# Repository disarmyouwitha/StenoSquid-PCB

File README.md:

# Steno Squid PCB

**ZMK firmware for StenoSquid-PCB!: https://github.com/disarmyouwitha/StenoSquid**

Steno Squid adds 16 MB (or 64MB) of flash for onboard stenography to your **Boardsource Wireless Corne SMT**.\
Steno Squid sits on top of the switch plate and connects through the eight-contact expansion slot.

## Choose a board

Both DIY boards use exposed SOIC leads and 0805 passives. Order a bare PCB using the ZIP for your chosen capacity and artwork.

| Capacity | Flash package | Board files | Parts | Est. total build (USD) |
|---|---|---|---|---:|
| **16 MB** | [Winbond W25Q128JVSIQ, SOIC-8 (208 mil)](https://www.digikey.com/en/products/detail/winbond-electronics/W25Q128JVSIQ-TR/5803944) | [White silkscreen ZIP](manufacturing/2026-11-18/diy-bare/stenosquid-16mb-diy-bare.zip) · [KiCad and fit template](variants/16mb-diy-soic/README.md) | [16 MB BOM](variants/16mb-diy-soic/BOM.csv) | **~$25** |
| **64 MB** | [Winbond W25Q512JVFIQ, SOIC-16 (300 mil)](https://www.digikey.com/en/products/detail/winbond-electronics/W25Q512JVFIQ/10244707) | [White silkscreen ZIP](manufacturing/2026-11-18/diy-bare/stenosquid-64mb-diy-bare.zip) · [KiCad and fit template](variants/64mb-diy-soic/README.md) | [64 MB BOM](variants/64mb-diy-soic/BOM.csv) | **~$35** |

### Parts for one board

| Ref. | Qty. | Part |
|---|---:|---|
| U1 | 1 | The Winbond flash listed for your PCB above |
| C1 | 1 | 100 nF X7R ceramic capacitor, 0805. BOM part Yageo [`CC0805KRX7R9BB104`](https://www.digikey.com/en/products/detail/yageo/CC0805KRX7R9BB104/302874) |
| R1 | 1 | 10 kΩ, 1% resistor, 0805. BOM part Yageo [`RC0805FR-0710KL`](https://www.digikey.com/en/products/detail/yageo/RC0805FR-0710KL/727535) |

## Factory-assembled 16 MB and 64 MB boards

The owner confirmed that both manufactured WSON boards worked. These low-profile builds have assembly packages for the flash, decoupling capacitor and CS# pull-up. Everything you need to have JLPCB manufacture it for you! (This was [much more expensive](https://github.com/disarmyouwitha/StenoSquid-PCB/blob/main/manufacturing/2026-11-18/cart-preview.jpg) than the DIY build!)

| **16 MB · White silkscreen** | **64 MB · Gold ENIG artwork** |
|---|---|
|  |  |
| [KiCad and BOM](pcb/README.md) · [Gerber ZIP](manufacturing/2026-11-18/16mb-silkscreen/16mb-silkscreen-gerbers.zip) · [BOM and placement](manufacturing/2026-11-18/16mb-silkscreen/) | [KiCad and BOM](variants/64mb-enig/README.md) · [Gerber ZIP](manufacturing/2026-11-18/64mb-gold/64mb-gold-gerbers.zip) · [BOM and placement](manufacturing/2026-11-18/64mb-gold/) |

## Host wiring

Viewed from above, the contacts run along the bottom with pin 1 on the left.

| Contact | Host GPIO or rail | Signal |
|---|---|---|
| 1 | P0.07 | CS# |
| 2 | P0.21 | IO0 |
| 3 | P0.12 | IO3 |
| 4 | P0.23 | IO1 |
| 5 | VCC switched by P0.31 | VCC |
| 6 | GND | GND |
| 7 | P0.19 | CLK |
| 8 | P0.05 | IO2 |

## License

StenoSquid-PCB is open-source hardware licensed under the [CERN Open Hardware Licence Version 2 - Permissive (CERN-OHL-P-2.0)](LICENSE).

You are free to manufacture, modify, and sell these boards, subject to the license terms. Third-party artwork retain the respective rights and licenses.

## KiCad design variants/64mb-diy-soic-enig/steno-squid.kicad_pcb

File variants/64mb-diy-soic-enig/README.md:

# Steno Squid 64 MB DIY · gold ENIG

[KiCad project](steno-squid.kicad_pro) · [Bare-board ZIP](../../manufacturing/diy-enig/stenosquid-64mb-diy-enig-bare.zip) · [BOM](BOM.csv) · [Front](previews/front.png) · [Back](previews/back.png) · [Schematic](previews/steno-squid.svg) · [1:1 fit template](previews/plate-fit-1to1.svg) · [STEP](steno-squid.step) · [Validation](validation.json)

Order the bare-board ZIP with **black solder mask and ENIG surface finish**. Pop and the splats are exposed front copper with matching soldermask openings and a 1 mm front copper keepout. The [white silkscreen edition](../64mb-diy-soic/README.md) uses the same parts, connector and routing.

The 64 MB DIY production variant uses the **Winbond W25Q512JVFIQ** in a 300 mil SOIC-16 package. Its exposed gull-wing leads are on 1.27 mm pitch and there is no center pad. C1 is 100 nF and R1 is 10 kΩ, both 0805. C2 and R2 are omitted. Everything except the mating portion of the header mounts on the front. [Winbond pinout and package drawing, pp. 7 and 89](https://www.mouser.com/datasheet/2/949/Winbond_W25Q512JV_Datasheet-3240039.pdf).

The PCB is 21.78 × 44.82 mm and nominally 1.0 mm thick, with the same header centers as the 16 MB DIY board, with Pop in exposed gold. The chip can stand **2.64 mm above the PCB** and span **10.64 mm** across its leads. Use the actual-size template to check the outline, and the package dimensions or a real chip to check vertical clearance. The generic KiCad STEP model is for visualization.

| Host contact | Signal | SOIC-16 lead |
|---|---|---:|
| 1 | CS_N | 7 |
| 2 | IO0 | 15 |
| 3 | IO3 | 1 |
| 4 | IO1 | 8 |
| 5 | VCC_SW | 2 |
| 6 | GND | 10 |
| 7 | CLK | 16 |
| 8 | IO2 | 9 |

The dedicated RESET# lead (3) is tied to VCC_SW on the board. Leads 4–6 and 11–14 have isolated lands. Align U1's pin-1 indicator with the board's upper-left marker, tack one corner, check alignment, then solder the remaining leads. Inspect for bridges and verify continuity and no supply short before connecting to the host.

KiCad 10.0.7 reports zero ERC, DRC, unconnected items, and schematic parity issues with every category enabled. The [DIY validator](../../tools/check_diy_soic.py) also checks pad geometry, the header and flash pin maps, and the unchanged board outline. Final populated fit and powered bring-up are pending.

For first power-up, qualify the switched rail for this chip's 2.7–3.6 V range and its read/program/erase load. Check JEDEC ID `EF 40 20` and use firmware with 64 MiB support and four-byte addressing. Verify reads and writes across the `0x01000000` and `0x02000000` address boundaries and near the end of flash, including after power cycling. [Capacity and power review](../../docs/capacity-variants.md).

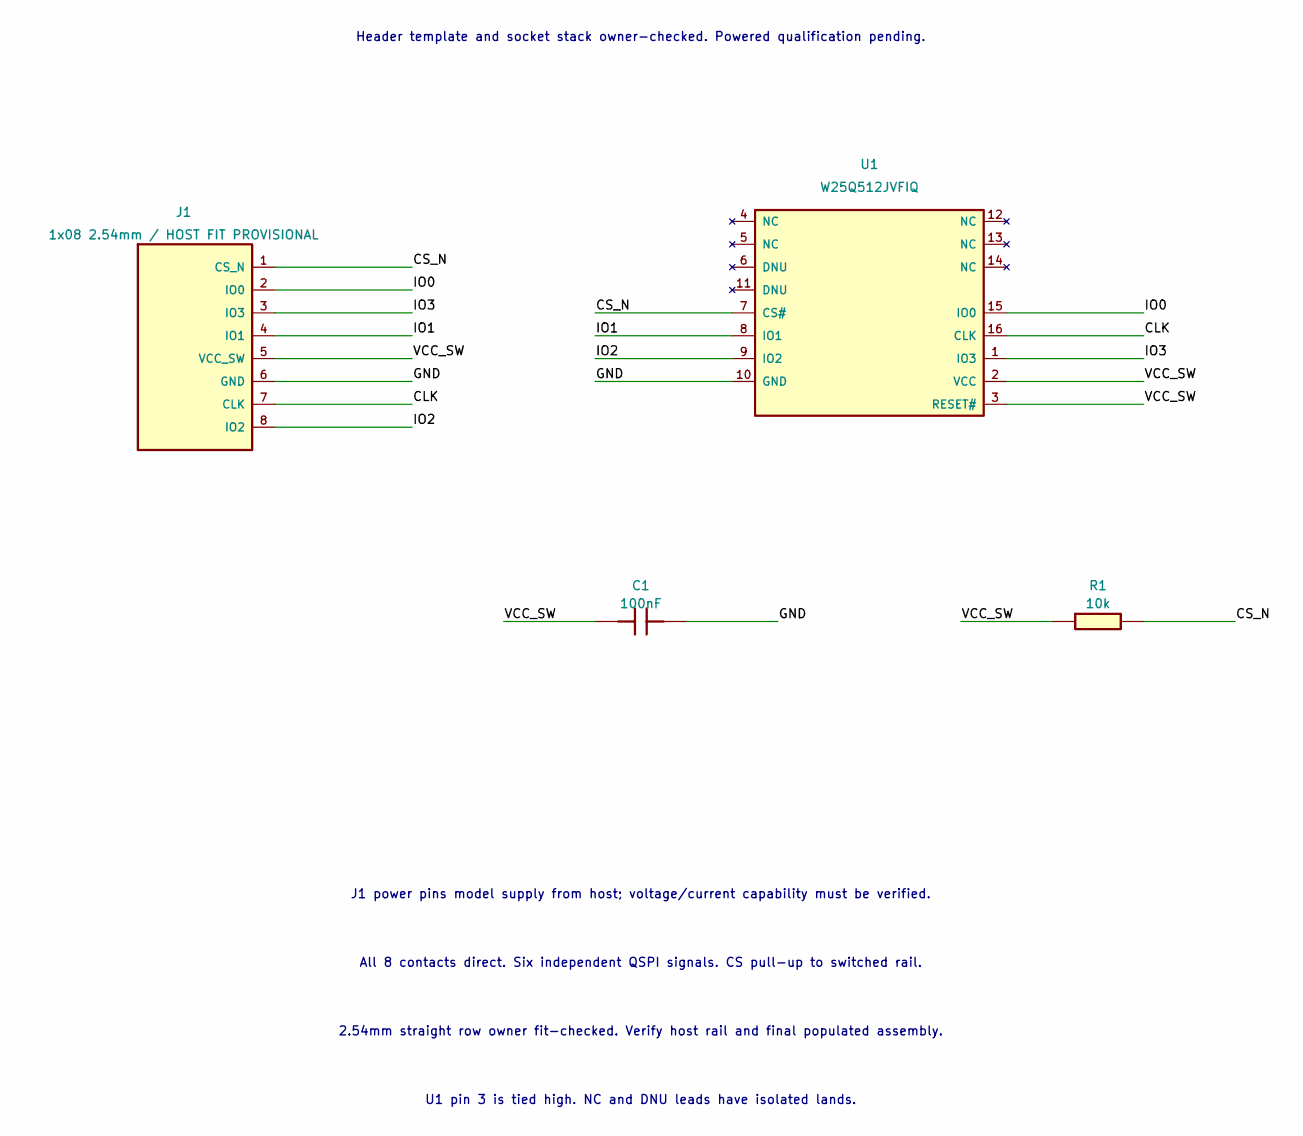
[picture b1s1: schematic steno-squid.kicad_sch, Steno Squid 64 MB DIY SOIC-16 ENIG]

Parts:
C1: 100nF; C_0805_2012Metric
J1: 1x08 2.54mm / HOST FIT PROVISIONAL; PinHeader_1x08_P2.54mm_Vertical
R1: 10k; R_0805_2012Metric
U1: W25Q512JVFIQ; SOIC-16W_7.5x10.3mm_P1.27mm

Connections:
/CLK: J1.7 (CLK), U1.16 (CLK)
/CS_N: J1.1 (CS_N), R1.2, U1.7 (CS#)
/GND: C1.2, J1.6 (GND), U1.10 (GND)
/IO0: J1.2 (IO0), U1.15 (IO0)
/IO1: J1.4 (IO1), U1.8 (IO1)
/IO2: J1.8 (IO2), U1.9 (IO2)
/IO3: J1.3 (IO3), U1.1 (IO3)
/VCC_SW: C1.1, J1.5 (VCC_SW), R1.1, U1.2 (VCC), U1.3 (RESET#)

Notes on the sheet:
Header template and socket stack owner-checked. Powered qualification pending.
J1 power pins model supply from host; voltage/current capability must be verified.
All 8 contacts direct. Six independent QSPI signals. CS pull-up to switched rail.
2.54mm straight row owner fit-checked. Verify host rail and final populated assembly.
U1 pin 3 is tied high. NC and DNU leads have isolated lands.

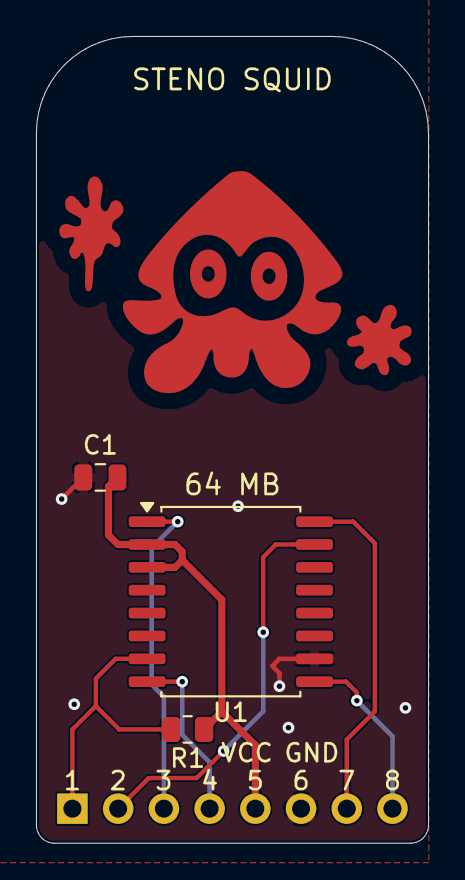
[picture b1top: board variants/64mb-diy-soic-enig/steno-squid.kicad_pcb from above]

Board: 2 copper layers, 21.8 x 44.8 mm, 4 parts (0 on the bottom side), 8 nets.

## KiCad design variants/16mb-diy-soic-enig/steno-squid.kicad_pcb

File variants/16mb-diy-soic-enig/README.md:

# Steno Squid 16 MB DIY · gold ENIG

[KiCad project](steno-squid.kicad_pro) · [Bare-board ZIP](../../manufacturing/diy-enig/stenosquid-16mb-diy-enig-bare.zip) · [BOM](BOM.csv) · [Front](previews/front.png) · [Back](previews/back.png) · [Schematic](previews/steno-squid.svg) · [1:1 fit template](previews/plate-fit-1to1.svg) · [STEP](steno-squid.step) · [Validation](validation.json)

Order the bare-board ZIP with **black solder mask and ENIG surface finish**. Pop and the splats are exposed front copper with matching soldermask openings and a 1 mm front copper keepout. The [white silkscreen edition](../16mb-diy-soic/README.md) uses the same parts, connector and routing.

The 16 MB DIY production variant uses **Winbond W25Q128JVSIQ** in a 208 mil SOIC-8 package with exposed leads at 1.27 mm pitch. The leads span up to 8.10 mm across the package. [Winbond package drawing, section 10.1](https://www.mouser.com/datasheet/2/949/Winbond_Electronics_Corporation_09_06_2024_W25Q128-3501276.pdf) Fit the 100 nF C1 and 10 kΩ R1 in 0805. The board uses the shared **21.78 × 44.82 mm** outline, fixed header centres and exposed gold Pop artwork. C2 and R2 are omitted from this layout.

Use the [BOM](BOM.csv) for the parts and align U1 pin 1 with the board marker. Check for JEDEC ID `EF 40 18` and verify quad reads and writes on the assembled board.

KiCad reports zero ERC, DRC, unconnected items and schematic-parity issues with every category enabled. Final populated fit and powered bring-up are pending. [Electrical and RF review](../../docs/design-review.md)

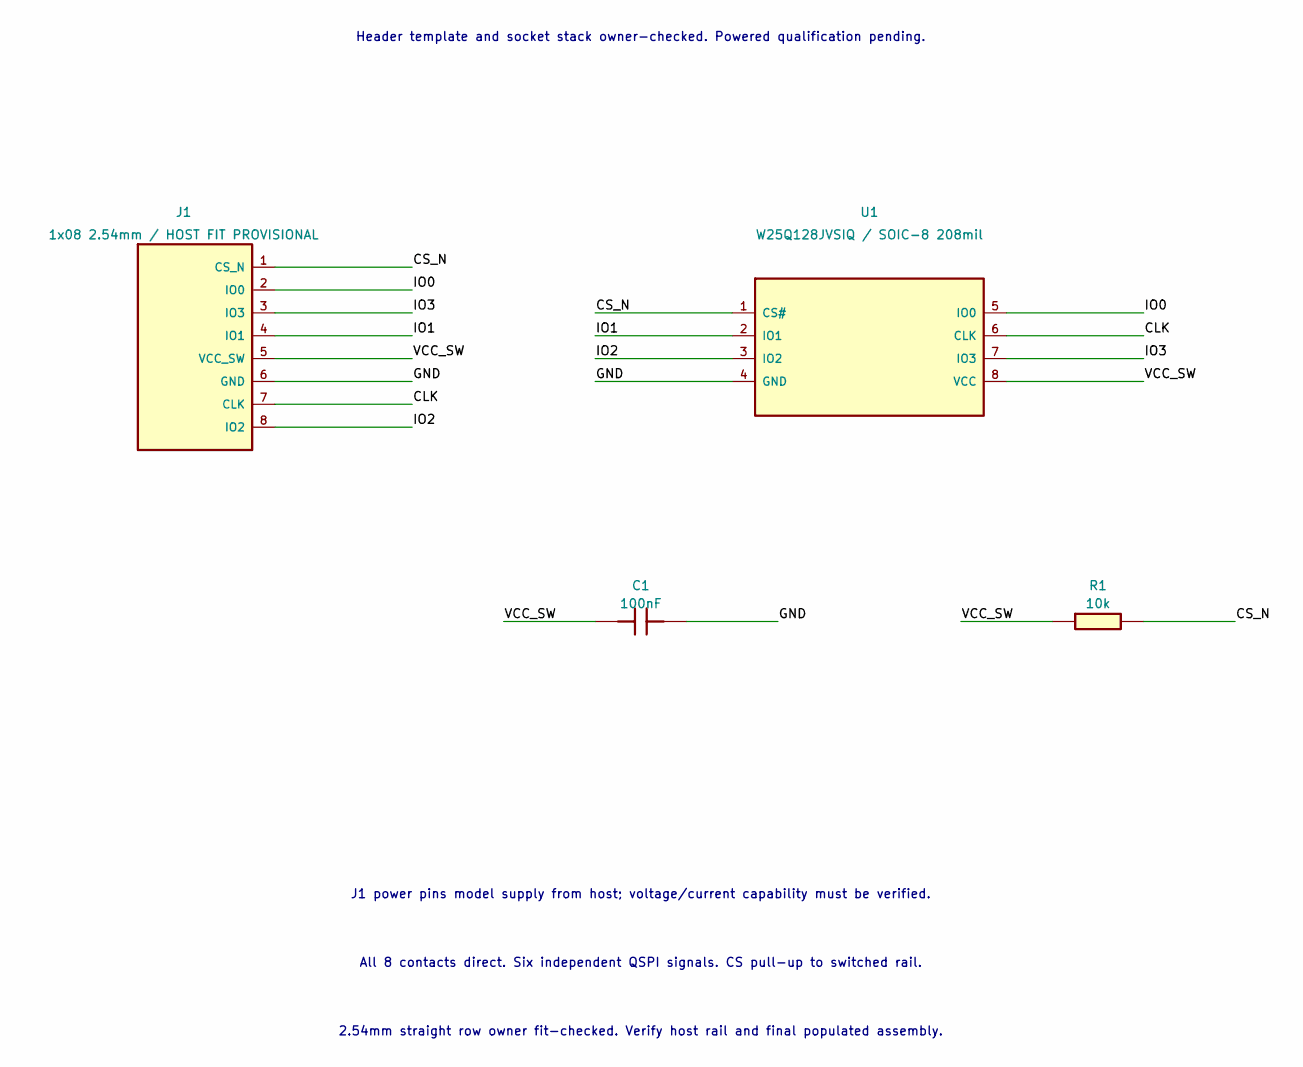
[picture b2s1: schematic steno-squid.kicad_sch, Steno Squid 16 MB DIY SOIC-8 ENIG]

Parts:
C1: 100nF; C_0805_2012Metric
J1: 1x08 2.54mm / HOST FIT PROVISIONAL; PinHeader_1x08_P2.54mm_Vertical
R1: 10k; R_0805_2012Metric
U1: W25Q128JVSIQ / SOIC-8 208mil; SOIC-8_5.3x5.3mm_P1.27mm

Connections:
/CLK: J1.7 (CLK), U1.6 (CLK)
/CS_N: J1.1 (CS_N), R1.2, U1.1 (CS#)
/GND: C1.2, J1.6 (GND), U1.4 (GND)
/IO0: J1.2 (IO0), U1.5 (IO0)
/IO1: J1.4 (IO1), U1.2 (IO1)
/IO2: J1.8 (IO2), U1.3 (IO2)
/IO3: J1.3 (IO3), U1.7 (IO3)
/VCC_SW: C1.1, J1.5 (VCC_SW), R1.1, U1.8 (VCC)

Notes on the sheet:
Header template and socket stack owner-checked. Powered qualification pending.
J1 power pins model supply from host; voltage/current capability must be verified.
All 8 contacts direct. Six independent QSPI signals. CS pull-up to switched rail.
2.54mm straight row owner fit-checked. Verify host rail and final populated assembly.

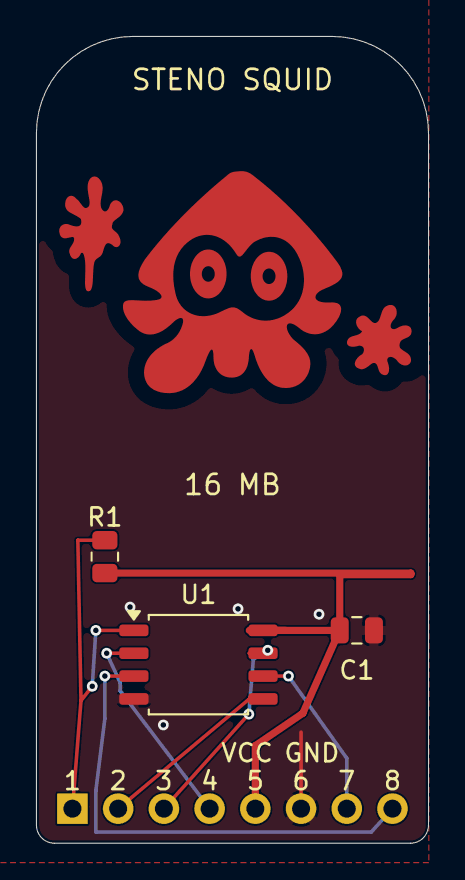
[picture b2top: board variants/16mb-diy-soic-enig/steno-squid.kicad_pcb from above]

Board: 2 copper layers, 21.8 x 44.8 mm, 4 parts (0 on the bottom side), 8 nets.
